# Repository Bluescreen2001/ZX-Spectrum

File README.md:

# ZX Spectrum addons

In this repository you find some addons which I created for the Sinclair ZX Spectrum computer

## DISCLAIMER:

This is for personal use only. You may not sell this design without contacting me.

## Description:

The Sinclair Spectrum was the first Sinclair computer which offers color. Besides that the biggest new feature comparing Sinclair's first computers ZX80 and ZX81 was the hardware video generation. The ZX80 and ZX81 have to generate the video signal by software which eats up most of the CPU time.
On the ZX Spectrum this was done by the hardware itself. So the CPU can run user programs at full speed. No Slow and Fast mode necessary.

There were several versions out there. The first one was the small "rubber keyboard" version. Very small, but only with a rubber keyboard. Then there where several versions with a keyboard with "real" buttons. 
But these were also only some real keycaps pressing on a keyboard foil. Better typing as on the rubber version, but not comparable to a keyboard with real switches.

The first addon I created was a keyboard PCB with real cherry switches. See the [SpectrumPlusKeyboard directory](SpectrumPlusKeyboard).

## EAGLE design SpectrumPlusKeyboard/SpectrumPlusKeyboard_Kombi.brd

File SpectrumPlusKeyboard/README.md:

# ZX Spectrum Plus Keyboard

This is a Spectrum Plus keyboard PCB with Cherry switches

## DISCLAIMER:

This is for personal use only. You may not sell this design without contacting me.

## Description:

Because my old ZX Spectrum Plus keyboard foil failed I designed a PCB as a replacement for the foil using Cherry MX or ML switches. You can fit it into the original ZX Spectrum Plus case if you like to modify the case.

## CAUTION: Using Cherry MX switches

If you want to put this into the original case there is a radical modification needed. You have to remove the complete mounting plate where all this white button stamps are fitted. Remove all keycaps and it's stamps, the saw out the mounting plate, leaving only the mounting taps for the screws. 
Then screw the PCB there and press all the keycaps onto the Cherry switches. The crosses for the keys are bit small, so you need a big amount of force to press them on. You will not be able to remove them without destroying the switches.

This variant gives the best typing result, but it is really complicated to put it into the case. So I would suggest this only for a cutsom made case, maybe recreate the Spectrum Plus from an old Spectrum PCB with a defective keyboard foil.

## Easyier: Using Cherry ML switches

These are the low profile keys. They are difficult to find. Maybe the easiest way is to buy an old Cherry low profile keyboard and unsolder the switches. If you want to put this into the original case, you have to file down the edges of the switches a bit, so that they fit into the round shafts 
where the white stamps of the original keyboard are located. Then mount the PCB instead of the foil. You have to use some washers to correct the height of the mounting tabs. The original keycaps will press the Cherry buttons by the white stamps of the original keyboard.
Alternatively to filing the edges of the switche, you can mill small edges into the case. I have an NC program for that include, see the TAP file. This modification is minimal and don't interfere with the use of the original keyboard foil in case you want to revert.

## Some advice for populating the PCB

In the first PCB revision I only had the very small resistor arrays, which are difficult to solder. In the current revision I added some 0805 resistors instead. Please only mount one of the two possibilities, single resitors OR resistor arrays.

Beware: there are two types of diodes which are named nearly identical, but they are not the same. Be sure to order the right ones and put them in the right places!

There are two sets of solder jumpers. With these you can swap the DELETE and BREAK keys.

For placing the switches exactly, I suggest to solder only one pin at first and then move them to the right position. With the low profile keys, solder one pin per key and place the PCB onto the case and verify all keys fit into the round shafts. Only then solder the remaining pins.

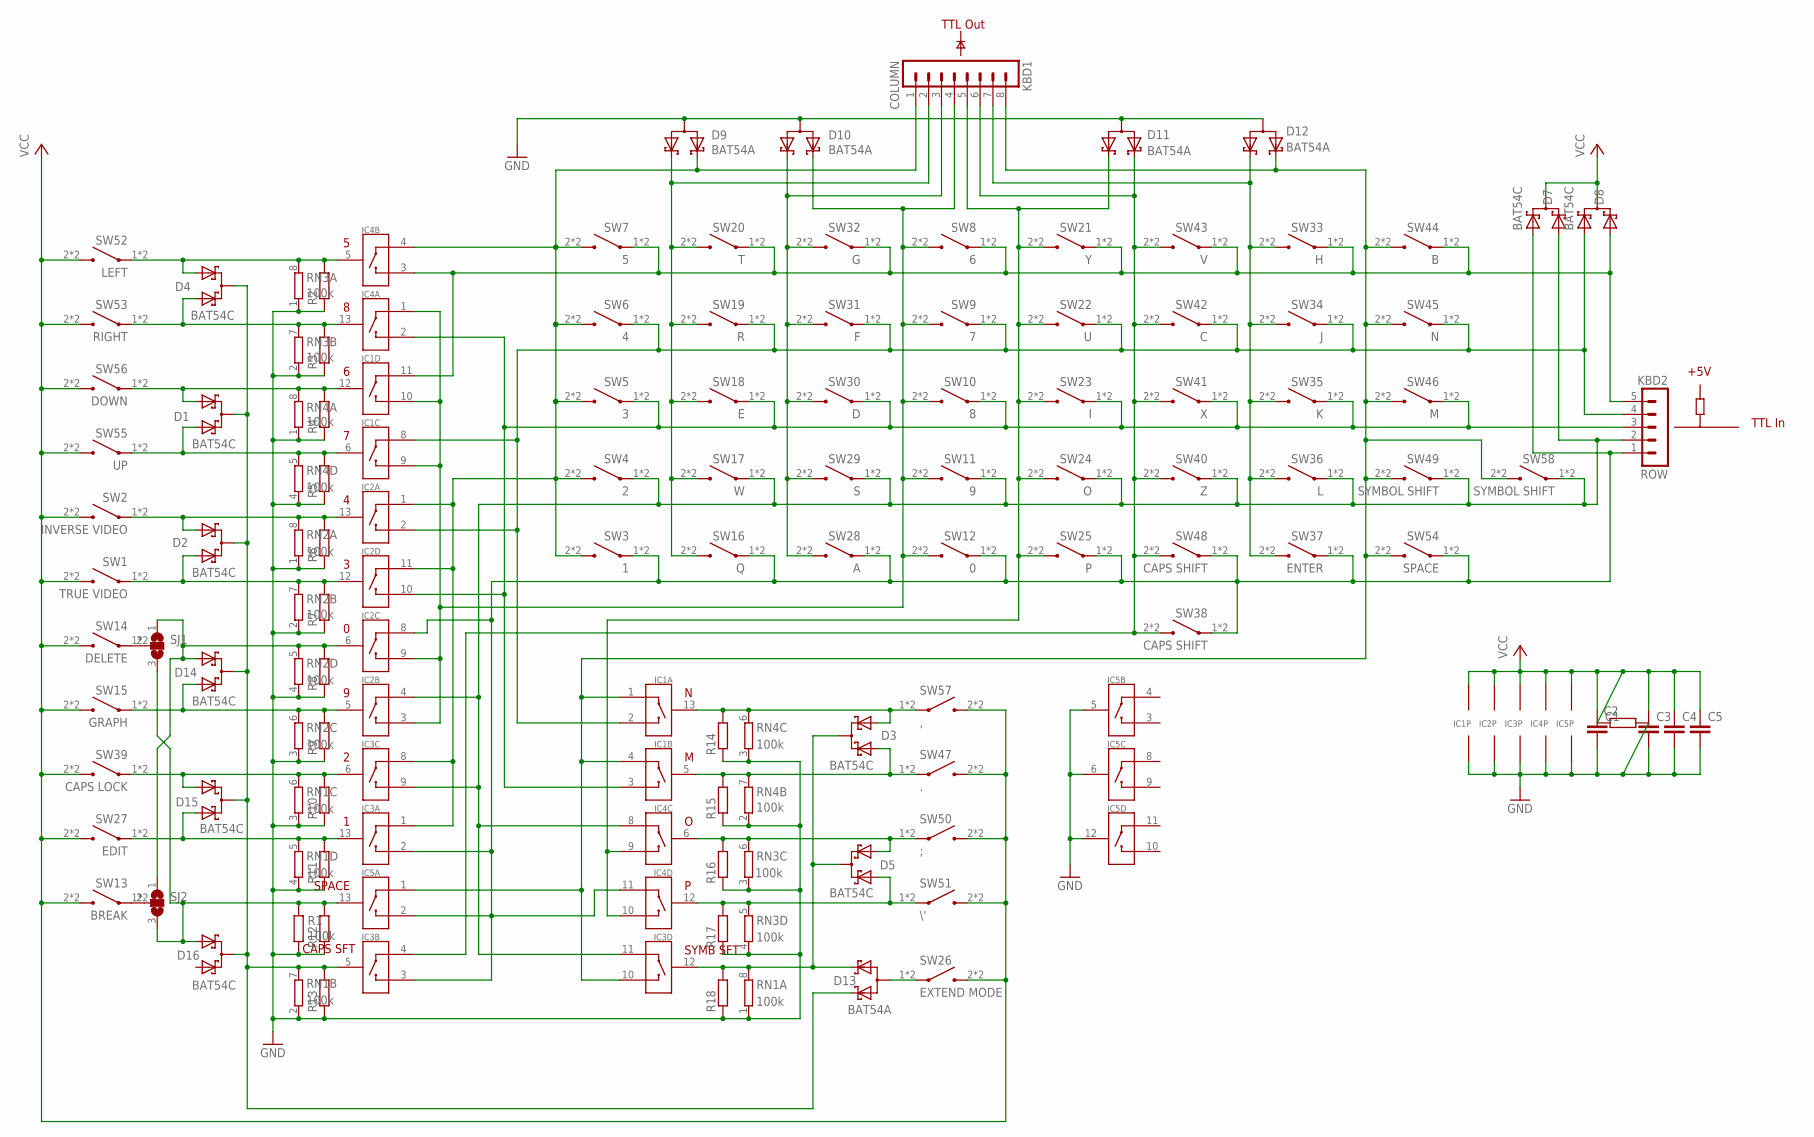
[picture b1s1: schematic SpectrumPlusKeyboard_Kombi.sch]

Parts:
C1, C3, C4, C5: C-EUC0805; C0805
C2: R-EU_R0805; R0805
D1, D2, D3, D4, D5, D7, D8, D14, D15, D16: BAT54C; SOT-23
D9, D10, D11, D12, D13: BAT54A; SOT-23
IC1, IC2, IC3, IC4, IC5: 4066; SO14
KBD1: COLUMN; MA08-1
KBD2: ROW; MA05-1
R1: 100k; R0805
R2, R3, R4, R5, R6, R7, R8, R9, R10, R11, R12, R13, R14, R15, R16, R17, R18: R-EU_R0805; R0805
RN1, RN2, RN3, RN4: 100k; 0603-ARC
SJ1, SJ2: SJ2W; SJ_2
SW1: TRUE VIDEO; ZX_1U_KOMBI
SW2: INVERSE VIDEO; ZX_1U_KOMBI
SW3: 1; ZX_1U_KOMBI
SW4: 2; ZX_1U_KOMBI
SW5: 3; ZX_1U_KOMBI
SW6: 4; ZX_1U_KOMBI
SW7: 5; ZX_1U_KOMBI
SW8: 6; ZX_1U_KOMBI
SW9: 7; ZX_1U_KOMBI
SW10: 8; ZX_1U_KOMBI
SW11: 9; ZX_1U_KOMBI
SW12: 0; ZX_1U_KOMBI
SW13: BREAK; ZX_1.5_KOMBI
SW14: DELETE; ZX_1.5_KOMBI
SW15: GRAPH; ZX_1U_KOMBI
SW16: Q; ZX_1U_KOMBI
SW17: W; ZX_1U_KOMBI
SW18: E; ZX_1U_KOMBI
SW19: R; ZX_1U_KOMBI
SW20: T; ZX_1U_KOMBI
SW21: Y; ZX_1U_KOMBI
SW22: U; ZX_1U_KOMBI
SW23: I; ZX_1U_KOMBI
SW24: O; ZX_1U_KOMBI
SW25: P; ZX_1U_KOMBI
SW26: EXTEND MODE; ZX_1.5_KOMBI
SW27: EDIT; ZX_1.25U_KOMBI
SW28: A; ZX_1U_KOMBI
SW29: S; ZX_1U_KOMBI
SW30: D; ZX_1U_KOMBI
SW31: F; ZX_1U_KOMBI
SW32: G; ZX_1U_KOMBI
SW33: H; ZX_1U_KOMBI
SW34: J; ZX_1U_KOMBI
SW35: K; ZX_1U_KOMBI
SW36: L; ZX_1U_KOMBI
SW37: ENTER; ZX_ENTER_KOMBI
SW38, SW48: CAPS SHIFT; ZX_2.3U_KOMBI
SW39: CAPS LOCK; ZX_1U_KOMBI
SW40: Z; ZX_1U_KOMBI
SW41: X; ZX_1U_KOMBI
SW42: C; ZX_1U_KOMBI
SW43: V; ZX_1U_KOMBI
SW44: B; ZX_1U_KOMBI
SW45: N; ZX_1U_KOMBI
SW46: M; ZX_1U_KOMBI
SW47: .; ZX_1U_KOMBI
SW49, SW58: SYMBOL SHIFT; ZX_1U_KOMBI
SW50: ;; ZX_1U_KOMBI
SW51: \'; ZX_1U_KOMBI
SW52: LEFT; ZX_1U_KOMBI
SW53: RIGHT; ZX_1U_KOMBI
SW54: SPACE; ZX_SPACE_KOMBI
SW55: UP; ZX_1U_KOMBI
SW56: DOWN; ZX_1U_KOMBI
SW57: ,; ZX_1U_KOMBI

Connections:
COL1: D9.1 (K1), IC2.1 (IO), IC2.11 (IO), IC3.1 (IO), IC3.8 (IO), IC4.4 (IO), KBD1.1, SW3.2, SW3.2B (2), SW4.2, SW4.2B (2), SW5.2, SW5.2B (2), SW6.2, SW6.2B (2), SW7.2, SW7.2B (2)
COL2: D9.2 (K2), KBD1.2, SW16.2, SW16.2B (2), SW17.2, SW17.2B (2), SW18.2, SW18.2B (2), SW19.2, SW19.2B (2), SW20.2, SW20.2B (2)
COL3: D10.2 (K2), KBD1.3, SW28.2, SW28.2B (2), SW29.2, SW29.2B (2), SW30.2, SW30.2B (2), SW31.2, SW31.2B (2), SW32.2, SW32.2B (2)
COL4: D10.1 (K1), IC1.9 (OI), IC1.10 (OI), IC2.3 (OI), IC2.9 (OI), IC4.1 (IO), KBD1.4, SW8.2, SW8.2B (2), SW9.2, SW9.2B (2), SW10.2, SW10.2B (2), SW11.2, SW11.2B (2), SW12.2, SW12.2B (2)
COL5: D11.1 (K1), IC4.9 (OI), IC4.10 (OI), KBD1.5, SW21.2, SW21.2B (2), SW22.2, SW22.2B (2), SW23.2, SW23.2B (2), SW24.2, SW24.2B (2), SW25.2, SW25.2B (2)
COL6: D11.2 (K2), IC3.4 (IO), KBD1.6, SW38.2, SW38.2B (2), SW40.2, SW40.2B (2), SW41.2, SW41.2B (2), SW42.2, SW42.2B (2), SW43.2, SW43.2B (2), SW48.2, SW48.2B (2)
COL7: D12.2 (K2), KBD1.7, SW33.2, SW33.2B (2), SW34.2, SW34.2B (2), SW35.2, SW35.2B (2), SW36.2, SW36.2B (2), SW37.2, SW37.2B (2)
COL8: D12.1 (K1), IC1.1 (IO), IC1.4 (IO), IC3.10 (OI), IC5.1 (IO), KBD1.8, SW44.2, SW44.2B (2), SW45.2, SW45.2B (2), SW46.2, SW46.2B (2), SW49.2, SW49.2B (2), SW54.2, SW54.2B (2), SW58.2, SW58.2B (2)
GND: C1.2, C2.2, C3.2, C4.2, C5.2, D9.3 (AA), D10.3 (AA), D11.3 (AA), D12.3 (AA), IC1.7 (GND), IC2.7 (GND), IC3.7 (GND), IC4.7 (GND), IC5.5 (C), IC5.6 (C), IC5.7 (GND), IC5.12 (C), R1.1, R2.1, R3.1, R4.1, R5.1, R6.1, R7.1, R8.1, R9.1, R10.1, R11.1, R12.1, R13.1, R14.1, R15.1, R16.1, R17.1, R18.1, RN1.1, RN1.2 (1), RN1.3 (1), RN1.4 (1), RN2.1, RN2.2 (1), RN2.3 (1), RN2.4 (1), RN3.1, RN3.2 (1), RN3.3 (1), RN3.4 (1), RN4.1, RN4.2 (1), RN4.3 (1), RN4.4 (1)
unnamed: SJ1.2, SW14.1, SW14.1B (1)
unnamed: SJ2.2, SW13.1, SW13.1B (1)
unnamed: D13.3 (AA), SW26.1, SW26.1B (1)
ROW1: D8.2 (A2), IC1.11 (IO), IC4.3 (OI), KBD2.5, SW7.1, SW7.1B (1), SW8.1, SW8.1B (1), SW20.1, SW20.1B (1), SW21.1, SW21.1B (1), SW32.1, SW32.1B (1), SW33.1, SW33.1B (1), SW43.1, SW43.1B (1), SW44.1, SW44.1B (1)
ROW2: D8.1 (A1), IC1.2 (OI), IC1.8 (IO), IC2.2 (OI), KBD2.4, SW6.1, SW6.1B (1), SW9.1, SW9.1B (1), SW19.1, SW19.1B (1), SW22.1, SW22.1B (1), SW31.1, SW31.1B (1), SW34.1, SW34.1B (1), SW42.1, SW42.1B (1), SW45.1, SW45.1B (1)
ROW3: IC1.3 (OI), IC2.10 (OI), IC4.2 (OI), KBD2.3, SW5.1, SW5.1B (1), SW10.1, SW10.1B (1), SW18.1, SW18.1B (1), SW23.1, SW23.1B (1), SW30.1, SW30.1B (1), SW35.1, SW35.1B (1), SW41.1, SW41.1B (1), SW46.1, SW46.1B (1)
ROW4: D7.2 (A2), IC2.4 (IO), IC3.9 (OI), IC3.11 (IO), IC4.8 (IO), KBD2.2, SW4.1, SW4.1B (1), SW11.1, SW11.1B (1), SW17.1, SW17.1B (1), SW24.1, SW24.1B (1), SW29.1, SW29.1B (1), SW36.1, SW36.1B (1), SW40.1, SW40.1B (1), SW49.1, SW49.1B (1), SW58.1, SW58.1B (1)
ROW5: D7.1 (A1), IC2.8 (IO), IC3.2 (OI), IC3.3 (OI), IC4.11 (IO), IC5.2 (OI), KBD2.1, SW3.1, SW3.1B (1), SW12.1, SW12.1B (1), SW16.1, SW16.1B (1), SW25.1, SW25.1B (1), SW28.1, SW28.1B (1), SW37.1, SW37.1B (1), SW38.1, SW38.1B (1), SW48.1, SW48.1B (1), SW54.1, SW54.1B (1)
SW0: D14.1 (A1), IC2.6 (C), R8.2, RN2.5 (2), SJ1.1, SJ2.1
SW1: D15.1 (A1), IC3.13 (C), R11.2, RN1.5 (2), SW27.1, SW27.1B (1)
SW2: D15.2 (A2), IC3.6 (C), R10.2, RN1.6 (2), SW39.1, SW39.1B (1)
SW3: D2.2 (A2), IC2.12 (C), R7.2, RN2.7 (2), SW1.1, SW1.1B (1)
SW4: D2.1 (A1), IC2.13 (C), R6.2, RN2.8 (2), SW2.1, SW2.1B (1)
SW5: D4.1 (A1), IC4.5 (C), R2.2, RN3.8 (2), SW52.1, SW52.1B (1)
SW6: D1.1 (A1), IC1.12 (C), R4.2, RN4.8 (2), SW56.1, SW56.1B (1)
SW7: D1.2 (A2), IC1.6 (C), R5.2, RN4.5 (2), SW55.1, SW55.1B (1)
SW8: D4.2 (A2), IC4.13 (C), R3.2, RN3.7 (2), SW53.1, SW53.1B (1)
SW9: D14.2 (A2), IC2.5 (C), R9.2, RN2.6 (2), SW15.1, SW15.1B (1)
SWCSHFT: D1.3 (CC), D2.3 (CC), D4.3 (CC), D13.2 (K2), D14.3 (CC), D15.3 (CC), D16.3 (CC), IC3.5 (C), R13.2, RN1.7 (2)
SWM: D3.2 (A2), IC1.5 (C), R15.2, RN4.7 (2), SW47.1, SW47.1B (1)
SWN: D3.1 (A1), IC1.13 (C), R14.2, RN4.6 (2), SW57.1, SW57.1B (1)
SWO: D5.2 (A2), IC4.6 (C), R16.2, RN3.6 (2), SW50.1, SW50.1B (1)
SWP: D5.1 (A1), IC4.12 (C), R17.2, RN3.5 (2), SW51.1, SW51.1B (1)
SWSPC: D16.1 (A1), IC5.13 (C), R1.2, R12.2, SJ1.3, SJ2.3
SWSSHFT: D3.3 (CC), D5.3 (CC), D13.1 (K1), IC3.12 (C), R18.2, RN1.8 (2)
VCC: C1.1, C2.1, C3.1, C4.1, C5.1, D7.3 (CC), D8.3 (CC), IC1.14 (VCC), IC2.14 (VCC), IC3.14 (VCC), IC4.14 (VCC), IC5.14 (VCC), SW1.2, SW1.2B (2), SW2.2, SW2.2B (2), SW13.2, SW13.2B (2), SW14.2, SW14.2B (2), SW15.2, SW15.2B (2), SW26.2, SW26.2B (2), SW27.2, SW27.2B (2), SW39.2, SW39.2B (2), SW47.2, SW47.2B (2), SW50.2, SW50.2B (2), SW51.2, SW51.2B (2), SW52.2, SW52.2B (2), SW53.2, SW53.2B (2), SW55.2, SW55.2B (2), SW56.2, SW56.2B (2), SW57.2, SW57.2B (2)

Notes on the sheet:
SYMB SFT
CAPS SFT
SPACE
TTL Out
TTL In
+5V

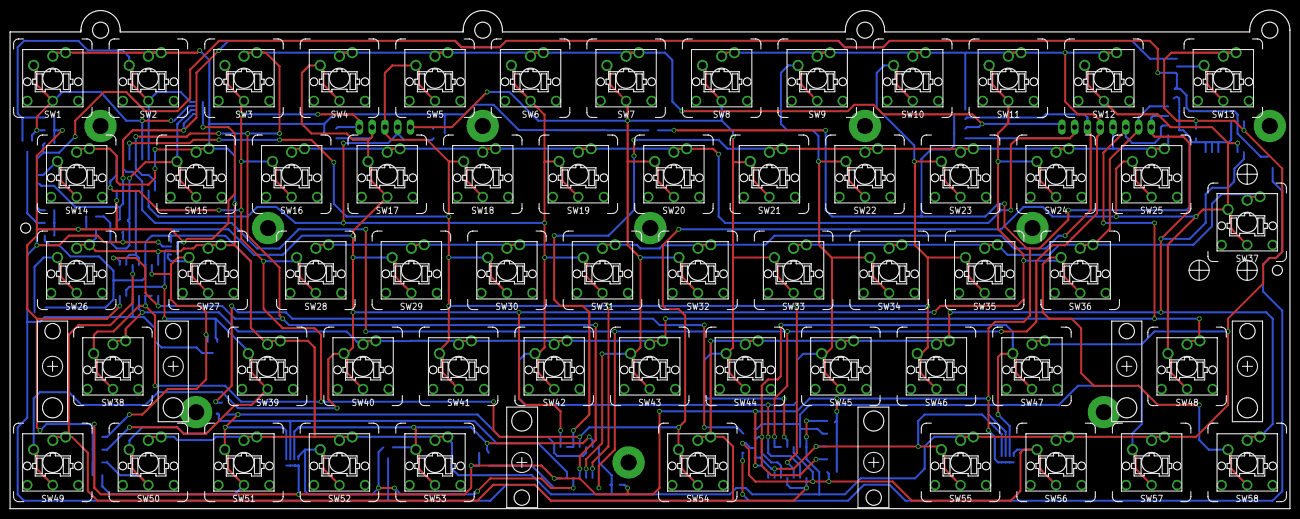
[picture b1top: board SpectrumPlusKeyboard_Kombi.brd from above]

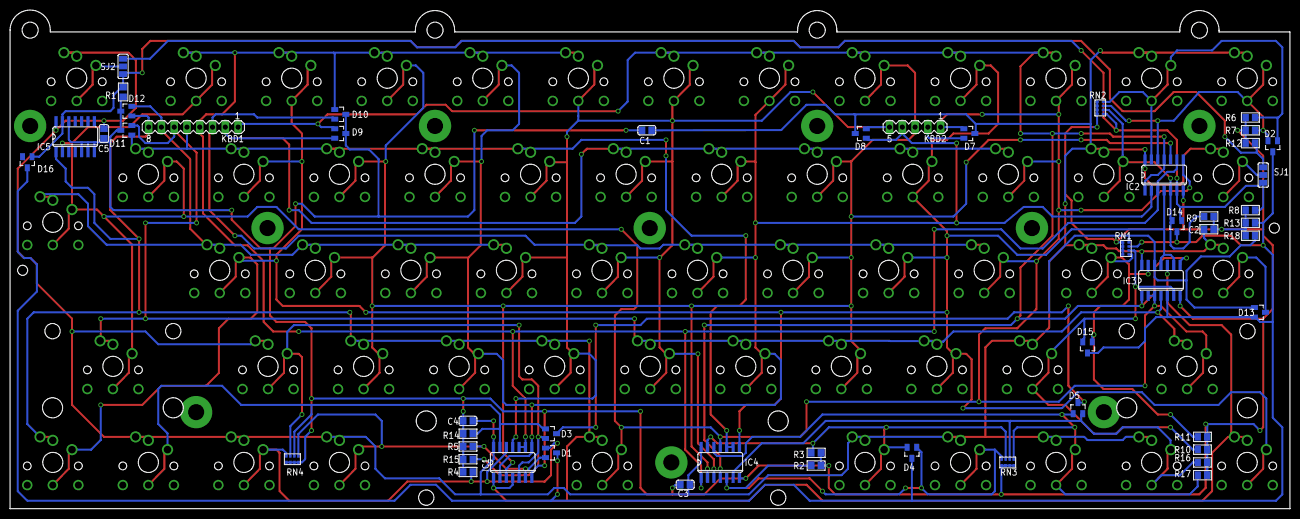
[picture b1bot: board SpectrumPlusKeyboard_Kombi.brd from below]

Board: 2 copper layers, 254.5 x 99.2 mm, 109 parts (51 on the bottom side), 35 nets.

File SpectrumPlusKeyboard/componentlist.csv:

#
# Spectrum Plus Keyboard
#

# PCB outline
 -9.20 ; -9.20 ; 246.70 ; -9.20 ; 246.70 ; 85.60 ; -9.20; 85.60 ; -9.20 ; -9.20
 
# Key coordinates
  0.00 ; 76.40 ; "TRUE Video"
 19.00 ; 76.40 ; "INV Video"
 38.02 ; 76.40 ; "1"
 57.00 ; 76.40 ; "2"
 76.00 ; 76.40 ; "3"
 95.00 ; 76.40 ; "4"
114.00 ; 76.40 ; "5"
133.00 ; 76.40 ; "6"
152.00 ; 76.40 ; "7"
171.00 ; 76.40 ; "8"
190.00 ; 76.40 ; "9"
209.00 ; 76.40 ; "0"
232.75 ; 76.40 ; "BREAK"

  4.75 ; 57.30 ; "DELETE"
 28.50 ; 57.30 ; "GRAPH"
 47.50 ; 57.30 ; "Q"
 66.50 ; 57.30 ; "W"
 85.50 ; 57.30 ; "E"
104.50 ; 57.30 ; "R"
123.50 ; 57.30 ; "T"
142.50 ; 57.30 ; "Y"
161.50 ; 57.30 ; "U"
180.50 ; 57.30 ; "I"
199.50 ; 57.30 ; "O"
218.50 ; 57.30 ; "P"

  4.75 ; 38.20 ; "EXTEND MODE"
 30.90 ; 38.20 ; "EDIT"
 52.30 ; 38.20 ; "A"
 71.30 ; 38.20 ; "S"
 90.30 ; 38.20 ; "D"
109.30 ; 38.20 ; "F"
128.30 ; 38.20 ; "G"
147.30 ; 38.20 ; "H"
166.30 ; 38.20 ; "J"
185.30 ; 38.20 ; "K"
204.30 ; 38.20 ; "L"
237.50 ; 47.75 ; "ENTER"

 11.95 ; 19.10 ; "CAPS SHIFT"
 42.70 ; 19.10 ; "CAPS LOCK"
 61.70 ; 19.10 ; "Z"
 80.70 ; 19.10 ; "X"
 99.70 ; 19.10 ; "C"
118.70 ; 19.10 ; "V"
137.70 ; 19.10 ; "B"
156.70 ; 19.10 ; "N"
175.70 ; 19.10 ; "M"
194.70 ; 19.10 ; "."
225.55 ; 19.10 ; "CAPS SHIFT"

  0.00 ;  0.00 ; "SYMBOL SHIFT"
 19.00 ;  0.00 ; ";"
 38.00 ;  0.00 ; "\""
 57.00 ;  0.00 ; "LEFT"
 76.00 ;  0.00 ; "RIGHT"
128.25 ;  0.00 ; "SPACE"
180.50 ;  0.00 ; "UP"
199.50 ;  0.00 ; "DOWN"
218.50 ;  0.00 ; ","
237.50 ;  0.00 ; "SYMBOL SHIFT"

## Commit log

2023-09-24 Initial upload
    This is a Spectrum Plus keyboard with Cherry switches
2023-09-24 Added some pictures
2023-09-24 Update README.md
    Correct picture path
2023-12-24 Corrected Error around SW9
